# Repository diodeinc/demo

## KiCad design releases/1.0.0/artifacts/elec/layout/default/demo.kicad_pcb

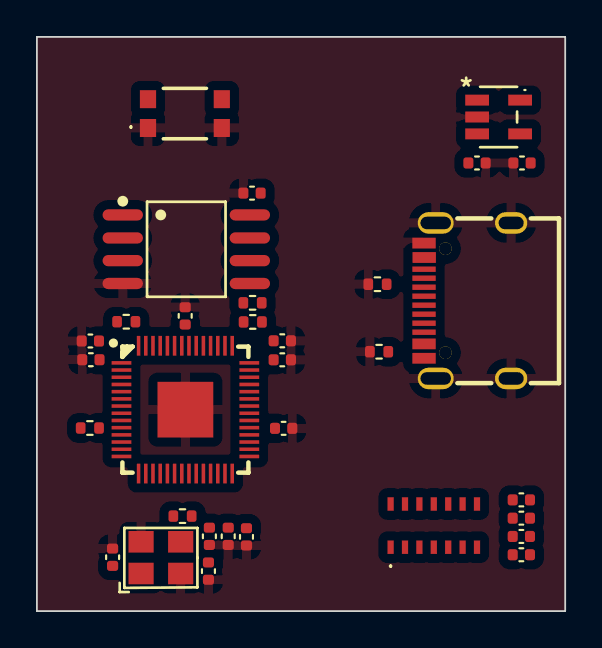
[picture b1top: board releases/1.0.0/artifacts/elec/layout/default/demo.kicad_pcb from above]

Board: 4 copper layers, 29.3 x 31.9 mm, 32 parts (0 on the bottom side), 25 nets, no tracks yet.

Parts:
C1, C2, C14, C18: 25V 1uF X5R ±10% 0402 Multilayer Ceramic Capacito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; C0402
C3: 6.3V 10uF X5R ±20% 0402 Multilayer Ceramic Capaci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; C0402
C4, C6, C9, C10, C11, C12, C13, C15, C16, C17: 16V 100nF X7R ±10% 0402 Multilayer Ceramic Capaci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; C0402
C5: 10V 4.7uF X5R ±20% 0402 Multilayer Ceramic Capaci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; C0402
C7, C8: 50V 22pF C0G ±5% 0402 Multilayer Ceramic Capacito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; C0402
R1, R2: 62.5mW Thick Film Resistors 50V ±100ppm/℃ ±1% 4.7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; R0402
R3, R4: 62.5mW Thick Film Resistors 50V ±100ppm/℃ ±1% 10k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; R0402
R5: 62.5mW Thick Film Resistors 50V ±100ppm/℃ ±1% 1kΩ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; R0402
R6, R7: 62.5mW Thick Film Resistors 50V ±100ppm/℃ ±1% 27Ω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; R0402
U1: ?; USB-C-SMD_KH-TYPE-C-16P
U2: ?; SOT-23-5_RIT
U3: ?; MAX30102EFDT
U4: ?; LQFN-56_L7.0-W7.0-P0.4-EP
U5: KMR211NGLFS (Tactile Switches); KMR211NGLFS
U6: ?; OSC-SMD_4P-L3.2-W2.5-BL
U7: ?; SOIC-8_L5.3-W5.3-P1.27-LS8.0-BL

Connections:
cc1: R1.1, U1.A5
cc2: R2.1, U1.B5
dm: R7.1, U1.A7, U1.B7
dp: R6.2, U1.A6, U1.B6
io0: U4.53, U7.5
io1: U4.55, U7.2
io2: U4.54, U7.3
io3: U4.51, U7.7
microcontroller.rp2040-cs-1: R4.2, U4.56, U5.2, U5.3, U7.1
microcontroller.rp2040-sck-1: U4.52, U7.6
microcontroller.rp2040.micro-vcc: C15.1, C16.1, C17.1, C18.1, U4.23, U4.45, U4.50
out: C8.1, R5.2, U6.3
power_supply-vcc: C2.1, C9.1, C10.1, C11.1, C12.1, C13.1, C14.1, R3.1, R4.1, U2.5, U4.1, U4.10, U4.22, U4.33, U4.42, U4.43, U4.44, U4.48, U4.49, U7.8
run: R3.2, U4.26
scl: U3.2, U4.32
sda: U3.3, U4.31
sensor.sensor-gnd: C3.2, C4.2, C5.2, C6.2, U3.12
sensor.sensor-vcc: C3.1, C4.1, U3.11
sensor.sensor-vcc-1: C5.1, C6.1, U3.9, U3.10
usb_connector-gnd-1: C1.2, C2.2, C7.2, C8.2, C9.2, C10.2, C11.2, C12.2, C13.2, C14.2, C15.2, C16.2, C17.2, C18.2, R1.2, R2.2, U1.1, U1.2, U1.3, U1.4, U1.A1, U1.A12, U1.B1, U1.B12, U2.2, U4.19, U4.57, U5.1, U5.4, U6.2, U6.4, U7.4
usb_connector-vcc: C1.1, U1.A4, U1.A9, U1.B4, U1.B9, U2.1
usb_dm: R7.2, U4.46
usb_dp: R6.1, U4.47
xin: C7.1, U4.20, U6.1
xout: R5.1, U4.21

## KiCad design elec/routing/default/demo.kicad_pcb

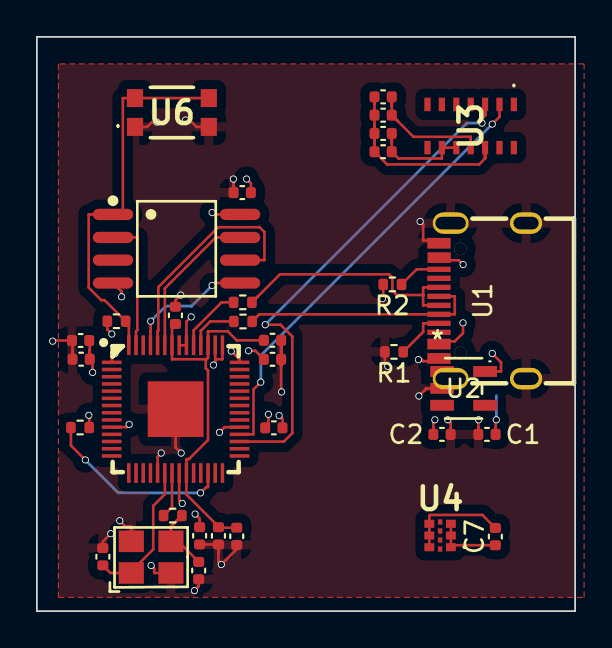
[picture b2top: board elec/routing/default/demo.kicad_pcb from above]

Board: 4 copper layers, 29.9 x 31.9 mm, 34 parts (0 on the bottom side), 27 nets.

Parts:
C1, C2, C15, C19: 25V 1uF X5R ±10% 0402 Multilayer Ceramic Capacito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; C0402
C3: 6.3V 10uF X5R ±20% 0402 Multilayer Ceramic Capaci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; C0402
C4, C6, C7, C10, C11, C12, C13, C14, C16, C17, C18: 16V 100nF X7R ±10% 0402 Multilayer Ceramic Capaci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; C0402
C5: 10V 4.7uF X5R ±20% 0402 Multilayer Ceramic Capaci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; C0402
C8, C9: 50V 20pF C0G ±5% 0402 Multilayer Ceramic Capacito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; C0402
R1, R2: 62.5mW Thick Film Resistors 50V ±100ppm/℃ ±1% 5.1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; R0402
R3, R4: 62.5mW Thick Film Resistors 50V ±100ppm/℃ ±1% 10k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; R0402
R5: 62.5mW Thick Film Resistors 50V ±100ppm/℃ ±1% 1kΩ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; R0402
R6, R7: 62.5mW Thick Film Resistors 50V ±100ppm/℃ ±1% 27Ω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; R0402
U1: ?; USB-C-SMD_KH-TYPE-C-16P
U2: ?; SOT-23-5_RIT
U3: ?; MAX30102EFDT
U4: ?; MAX30208CLBT
U5: ?; LQFN-56_L7.0-W7.0-P0.4-EP
U6: KMR211NGLFS (Tactile Switches); KMR211NGLFS
U7: ?; OSC-SMD_4P-L3.2-W2.5-BL
U8: ?; SOIC-8_L5.3-W5.3-P1.27-LS8.0-BL

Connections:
cc1: R1.1, U1.A5
cc2: R2.1, U1.B5
dm: R7.1, U1.A7, U1.B7
dp: R6.2, U1.A6, U1.B6
io0: U5.53, U8.5
io1: U5.55, U8.2
io2: U5.54, U8.3
io3: U5.51, U8.7
microcontroller.rp2040-cs-1: R4.2, U5.56, U6.2, U6.3, U8.1
microcontroller.rp2040-sck-1: U5.52, U8.6
microcontroller.rp2040.micro-vcc: C16.1, C17.1, C18.1, C19.1, U5.23, U5.45, U5.50
out: C9.1, R5.2, U7.3
power_supply-vcc: C2.1, C10.1, C11.1, C12.1, C13.1, C14.1, C15.1, R3.1, R4.1, U2.5, U5.1, U5.10, U5.22, U5.33, U5.42, U5.43, U5.44, U5.48, U5.49, U8.8
run: R3.2, U5.26
scl: U3.2, U4.9, U5.32
sda: U3.3, U4.8, U5.31
sensor-gnd: C7.2, U4.4, U4.5, U4.6
sensor.sensor-gnd: C3.2, C4.2, C5.2, C6.2, U3.12
sensor.sensor-vcc: C3.1, C4.1, U3.11
sensor.sensor-vcc-1: C5.1, C6.1, U3.9, U3.10
temperature_sensor.sensor-vcc: C7.1, U4.1, U4.2, U4.3
usb_connector-gnd-1: C1.2, C2.2, C8.2, C9.2, C10.2, C11.2, C12.2, C13.2, C14.2, C15.2, C16.2, C17.2, C18.2, C19.2, R1.2, R2.2, U1.1, U1.2, U1.3, U1.4, U1.A1, U1.A12, U1.B1, U1.B12, U2.2, U5.19, U5.57, U6.1, U6.4, U7.2, U7.4, U8.4
usb_connector-vcc: C1.1, U1.A4, U1.A9, U1.B4, U1.B9, U2.1
usb_dm: R7.2, U5.46
usb_dp: R6.1, U5.47
xin: C8.1, U5.20, U7.1
xout: R5.1, U5.21

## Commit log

2024-10-24 [DEMO] init
2024-10-24 [PCB] fix layout
2024-10-24 [PCB] add temp
2024-10-24 [PCB] route
2024-10-24 [DOCS] fix
2024-10-24 [ELEC] messed up layout
2024-11-11 [DEMO] fix lib
2024-11-19 [DEMO] tweaks
2024-12-11 [DEMO] better
2024-12-11 [ROUTE] fix
2024-12-23 [CURSOR] context
2025-01-09 [RELEASE] 1.0.0
2025-01-19 [CURSOR] update tools
2025-01-23 [AGENT] open
2025-01-23 [PCB] remove release
2025-02-27 [DOCS]
2025-03-07 [COMPONENTS] keep
2025-03-12 [DEMO] remove prompts
2025-03-12 [CURSOR] mcp
2025-03-13 [DOCS] add title
2025-03-16 [DOCS] blank
2025-03-19 release
2025-03-25 add cursor rules
2025-03-28 add schematics review
